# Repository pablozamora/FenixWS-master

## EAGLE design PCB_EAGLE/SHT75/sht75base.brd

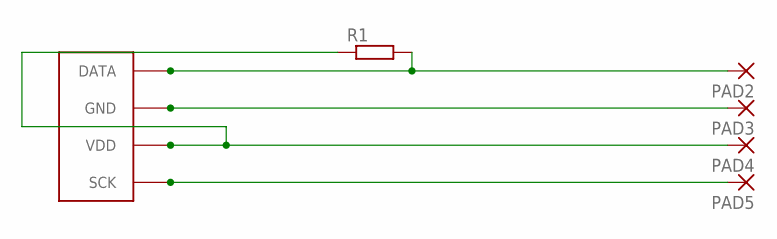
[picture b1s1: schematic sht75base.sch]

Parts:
PAD2, PAD3, PAD4, PAD5: 2,54/1,1
R1: R-EU_0309/10; 0309/10
U$2: SHT71; SHT7X

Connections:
unnamed: PAD4.1, R1.1, U$2.2 (VDD)
unnamed: PAD3.1, U$2.3 (GND)
unnamed: PAD2.1, R1.2, U$2.4 (DATA)
unnamed: PAD5.1, U$2.1 (SCK)

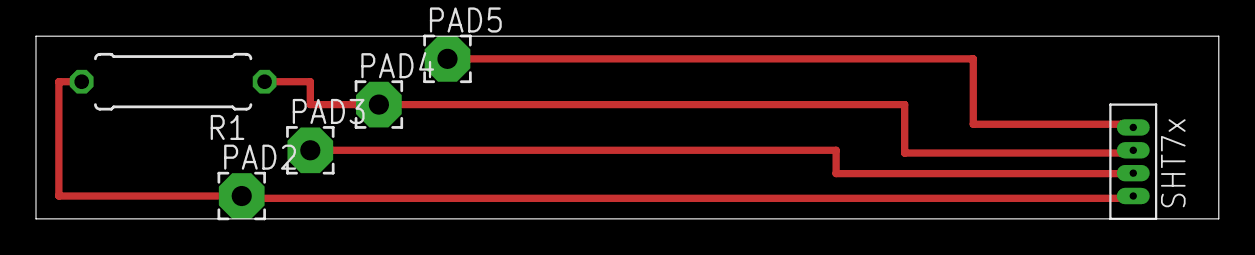
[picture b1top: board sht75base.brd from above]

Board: 2 copper layers, 65.7 x 10.2 mm, 6 parts (0 on the bottom side), 4 nets.

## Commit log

2015-05-16 Sensirion datasheet
2015-05-16 Datasheets
2015-05-16 :circus_tent: Added .gitattributes & .gitignore files
2015-05-16 Version 1
2015-05-16 Version 2
2015-05-16 Contabilidad
    Archivo en excel para ver movimiento de dinero
2015-05-16 Hola
    Hola
2015-05-16 Nothola
    Nothola
2015-05-16 Gastos al 16/05
    Compra de conversor de 420 mA a 0-5 V
2015-05-16 BorrandoBasura
    BorrandoBasura
2015-05-16 Códigos_Arduino1
    Códigos_Arduino1
2015-05-16 Datasheet_ss461c
    Datasheet_ss461c
2015-05-19 ADC_mejoras
2015-05-20 ADC_mejora2
2015-05-20 SD + Wifi
    Codigos de Pruebas sobre SD y WIFI
    Arduino
2015-05-20 WindSpeed
    versión funcional, sin calibración
2015-05-20 Costos
    Gastos al 20/05
2015-05-20 Facturas
    Facturas de costos de envío de sensores de viento, temp y humedad y
    lluvia. Facturas corresponden al servicio de JetBox
2015-05-20 ImagenRainGauge
2015-05-20 WindSpeed2.0
    Funcional pero sin calibración
2015-05-20 ADC_MEJORAS_DELAY
    ADC_MEJORAS_DELAY
2015-05-20 RainGauge
    RainGauge código de Arduino
2015-05-21 SHT75 versión1
    código sin probar y con otras cosas que no interesas.
2015-05-24 Imágenes
2015-05-26 Prueba_temboo
    Prueba_temboo
2015-05-26 Corrección_Prueba_Temboo
    Corrección_Prueba_Temboo
2015-05-30 FWS
    Código de viento y lluvia
2015-05-30 Actualización
    Código de radiación solar y unión con el de viento y lluvia
2015-06-01 temboo_viento_lluvia
    temboo_viento_lluvia
2015-06-03 temperatura
    temperatura
2015-06-03 temboo_todo
    temboo_todo
2015-06-03 Especificaciones_sensores
    Especificaciones técnicas de los sensores entregada al CATIE
2015-06-03 Informe
    Informe Final lab de micros
2015-06-03 Prospecto
    Prospectus ahí medio rralcha
2015-06-03 Informe
    Actualización Informe
2015-06-03 informe
    Informe Act
2015-06-03 Revert "informe"
    This reverts commit af11e5d41a674a21400498fd7883716520066965.
2015-06-03 Informe2
    Informe 2
2015-06-03 ConPortada
    informe modificacion de portada
2015-06-03 Prospecturs
    papaya
2015-06-10 Avance
    Documento para CATIE de avance hasta 10/06/2015
2015-06-13 varios
    muchos documentos actualizados
2015-06-16 Costos
    Actualización de la tabla de costos después de la compra del protector
    del sensor de temp y humedad
2015-06-23 documentos
    informe de graduación de un proyecto similar
2015-06-25 PCB eagle/ RCV420
    archivos para la impresion del PCB del SHT75 y conexiones del RCV420
2015-07-08 varios
    varios
2015-07-10 Prueba
    Prueba
2015-07-10 fotos
    fotos
2015-07-10 Jairol
    Jairol
2015-07-10 Union
    archivos arduino
2015-07-11 UnionFinal
    códigos de uniones finales y pruebas
2015-07-14 Varios
    Código Actualizado
2015-08-02 varas
    actualizaciones
